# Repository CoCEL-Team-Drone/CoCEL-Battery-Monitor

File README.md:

# CoCEL LiPo Battery Monitor

**A high-current LiPo battery monitor with individual cell voltage sensing**

[!IMPORTANT] 
This project is currently under development! Especially cell voltage monitoring circuit. Please stay tuned for future updates.

The CoCEL LiPo Battery Monitor is a dedicated power management and monitoring solution for multicopters. It measures total pack voltage, discharge current, and individual cell voltages, interfacing with a FC via UART.

## 1. Core Specifications

### Power
- **Voltage:** 4s~6s LiPo (14.8 V ~ 25.2 V)
- **Current:** 200 A continuous
- **Output Cutoff:** Main power output can be cut off via a physical arming switch (shorting pins) or via UART commands
- **Aux Power Output:**
    - 3.3 V (3 A)
    - 5 V (3 A)
    - Input Bypass: Dedicated power rail for an SBC (remains active even when the main output is cut off)

### Connectivity
- **Interfaces:** 
    - **Communication:** 1x UART
    - **Visual Feedback:** 1x Diagnostic LED
    - **Firmware update:** Test points are used for firmware updates (SWDIO, SWCLK, NRST).

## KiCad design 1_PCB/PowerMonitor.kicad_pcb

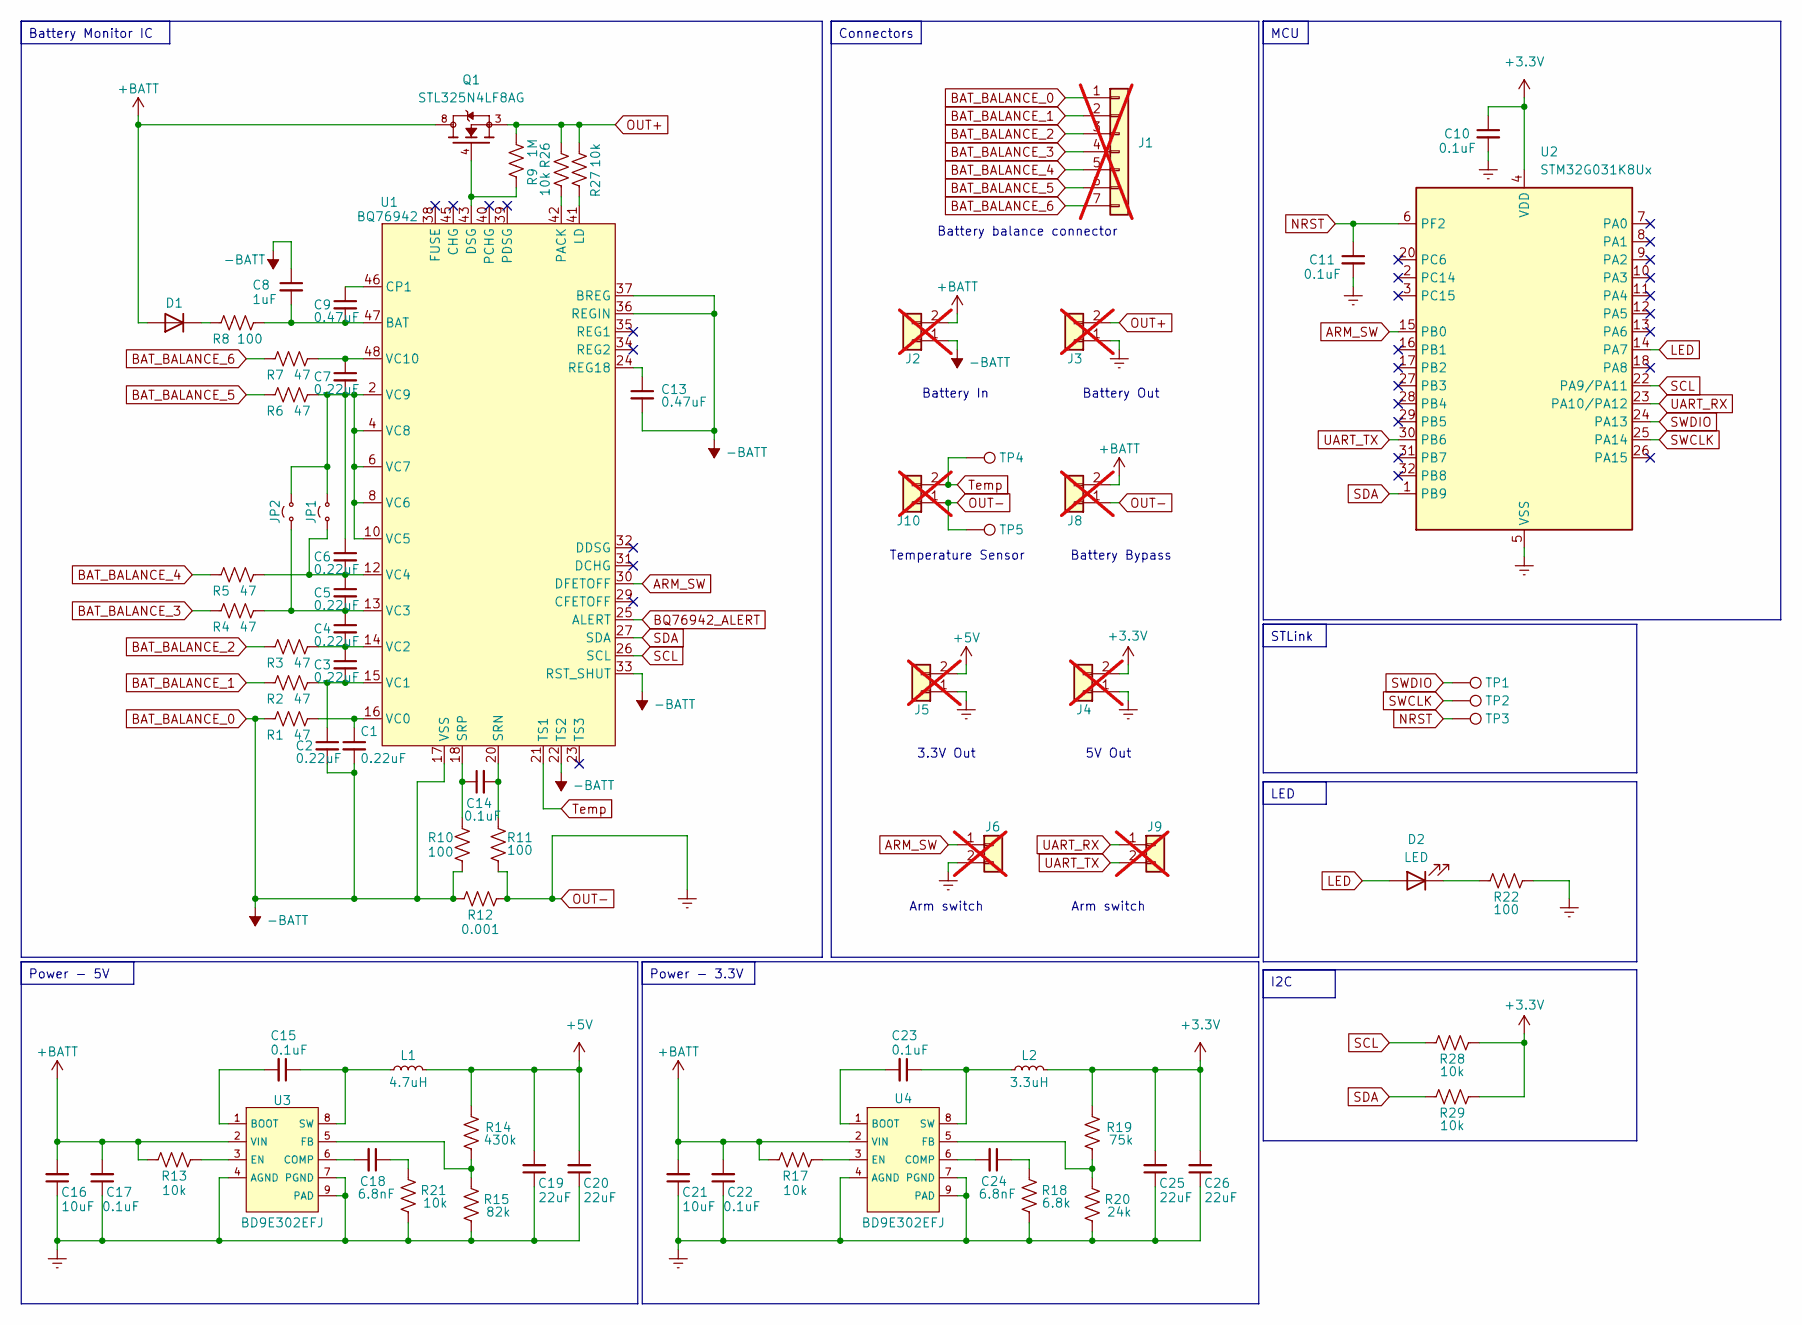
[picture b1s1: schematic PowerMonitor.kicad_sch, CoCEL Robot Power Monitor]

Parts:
C1, C2, C3, C4, C5, C6, C7: 0.22uF; C_0402_1005Metric
C8: 1uF; C_0402_1005Metric
C9, C13: 0.47uF; C_0402_1005Metric
C10, C11, C14: 0.1uF; C_0402_1005Metric
C15, C17, C22, C23: 0.1uF; C_0603_1608Metric
C16, C21: 10uF; C_1210_3225Metric
C18, C24: 6.8nF; C_0402_1005Metric_Pad0.74x0.62mm_HandSolder
C19, C20, C25, C26: 22uF; C_1210_3225Metric
D1: S1AFL; D_SOD-123
D2: LED; LED_0603_1608Metric
J1: Conn_01x07; Molex_KK-254_AE-6410-07A_1x07_P2.54mm_Vertical; not fitted
J2: Conn_01x02; AMASS_XT60-M_1x02_P7.20mm_Vertical; not fitted
J3: Conn_01x02; AMASS_XT60-F_1x02_P7.20mm_Vertical; not fitted
J4, J5, J6, J9, J10: Conn_01x02; PinHeader_1x02_P2.54mm_Vertical; not fitted
J8: Conn_01x02; AMASS_XT30U-F_1x02_P5.0mm_Vertical; not fitted
JP1, JP2: Jumper_2_Small_Open; SolderJumper-2_P1.3mm_Open_TrianglePad1.0x1.5mm
L1: 4.7uH; L_7.3x7.3_H4.5
L2: 3.3uH; L_7.3x7.3_H4.5
Q1: STL325N4LF8AG; ST_PowerFLAT-6L_5x6mm_P1.27mm
R1, R2, R3, R4, R5, R6, R7: 47; R_0402_1005Metric
R8, R10, R11, R22: 100; R_0402_1005Metric
R9: 1M; R_0402_1005Metric
R12: 0.001; R_3920_10052Metric
R13, R17, R21, R26, R27, R28, R29: 10k; R_0402_1005Metric
R14: 430k; R_0402_1005Metric
R15: 82k; R_0402_1005Metric
R18: 6.8k; R_0402_1005Metric
R19: 75k; R_0402_1005Metric
R20: 24k; R_0402_1005Metric
TP1, TP2, TP3, TP4, TP5: TestPoint; TestPoint_Pad_D1.0mm
U1: BQ76942; TQFP-48_7x7mm_P0.5mm
U2: STM32G031K8Ux; QFN-32-1EP_5x5mm_P0.5mm_EP3.45x3.45mm
U3, U4: BD9E302EFJ; HTSOP-8-1EP_3.9x4.9mm_P1.27mm_EP2.4x3.2mm

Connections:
+3.3V: C10.1, C25.2, C26.2, J4.2, L2.2, R19.2, R28.2, R29.2, U2.4 (VDD)
+5V: C19.2, C20.2, J5.2, L1.2, R14.2
+BATT: C16.2, C17.2, C21.2, C22.2, D1.2 (A), J2.2, J8.2, Q1.5, Q1.6, Q1.7, Q1.8, R13.1, R17.1, U3.2 (VIN), U4.2 (VIN)
ARM_SW: J6.1, U1.30 (DFETOFF), U2.15 (PB0)
BAT_BALANCE_0: C1.2, C2.2, C8.1, C13.2, J1.1, J2.1, R1.1, R10.2, R12.2, U1.17 (VSS), U1.22 (TS2), U1.33 (RST_SHUT), U1.36 (REGIN), U1.37 (BREG)
BAT_BALANCE_1: J1.2, R2.1
BAT_BALANCE_2: J1.3, R3.1
BAT_BALANCE_3: J1.4, R4.1
BAT_BALANCE_4: J1.5, R5.1
BAT_BALANCE_5: J1.6, R6.1
BAT_BALANCE_6: J1.7, R7.1
BQ76942_ALERT: U1.25 (ALERT)
LED: D2.2 (A), U2.14 (PA7)
NRST: C11.1, TP3.1 (1_1), U2.6 (PF2)
unnamed: C18.1, R21.2
unnamed: C24.1, R18.2
unnamed: D1.1 (K), R8.1
unnamed: D2.1 (K), R22.1
unnamed: C5.1, C6.2, JP1.1 (A), R5.2, U1.12 (VC4)
unnamed: C6.1, C7.2, JP1.2 (B), JP2.2 (B), R6.2, U1.2 (VC9), U1.4 (VC8), U1.6 (VC7), U1.8 (VC6), U1.10 (VC5)
unnamed: C4.1, C5.2, JP2.1 (A), R4.2, U1.13 (VC3)
unnamed: C8.2, C9.2, R8.2, U1.47 (BAT)
unnamed: C9.1, U1.46 (CP1)
unnamed: Q1.4, R9.1, U1.43 (DSG)
unnamed: R27.1, U1.41 (LD)
unnamed: R26.2, U1.42 (PACK)
unnamed: C13.1, U1.24 (REG18)
unnamed: C14.2, R11.2, U1.20 (SRN)
unnamed: C14.1, R10.1, U1.18 (SRP)
unnamed: C1.1, R1.2, U1.16 (VC0)
unnamed: C2.1, C3.2, R2.2, U1.15 (VC1)
unnamed: C3.1, C4.2, R3.2, U1.14 (VC2)
unnamed: C7.1, R7.2, U1.48 (VC10)
unnamed: C15.2, U3.1 (BOOT)
unnamed: C18.2, U3.6 (COMP)
unnamed: R13.2, U3.3 (EN)
unnamed: R14.1, R15.2, U3.5 (FB)
unnamed: C15.1, L1.1, U3.8 (SW)
unnamed: C23.2, U4.1 (BOOT)
unnamed: C24.2, U4.6 (COMP)
unnamed: R17.2, U4.3 (EN)
unnamed: R19.1, R20.2, U4.5 (FB)
unnamed: C23.1, L2.1, U4.8 (SW)
OUT+: J3.2, Q1.1, Q1.2, Q1.3, R9.2, R26.1, R27.2
OUT-: C10.2, C11.2, C16.1, C17.1, C19.1, C20.1, C21.1, C22.1, C25.1, C26.1, J3.1, J4.1, J5.1, J6.2, J8.1, J10.1, R11.1, R12.1, R15.1, R18.1, R20.1, R21.1, R22.2, TP5.1 (1_1), U2.5 (VSS), U2.33 (VSS), U3.4 (AGND), U3.7 (PGND), U3.9 (PAD), U4.4 (AGND), U4.7 (PGND), U4.9 (PAD)
SCL: R28.1, U1.26 (SCL), U2.22 (PA9/PA11)
SDA: R29.1, U1.27 (SDA), U2.1 (PB9)
SWCLK: TP2.1 (1_1), U2.25 (PA14)
SWDIO: TP1.1 (1_1), U2.24 (PA13)
Temp: J10.2, TP4.1 (1_1), U1.21 (TS1)
UART_RX: J9.1, U2.23 (PA10/PA12)
UART_TX: J9.2, U2.30 (PB6)

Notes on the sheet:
Battery balance connector
Temperature Sensor
Arm switch
Battery Bypass
Battery Out
Battery In
5V Out
3.3V Out
Battery Monitor IC
STLink
LED
Power - 5V
Connectors
I2C
Power - 3.3V
MCU

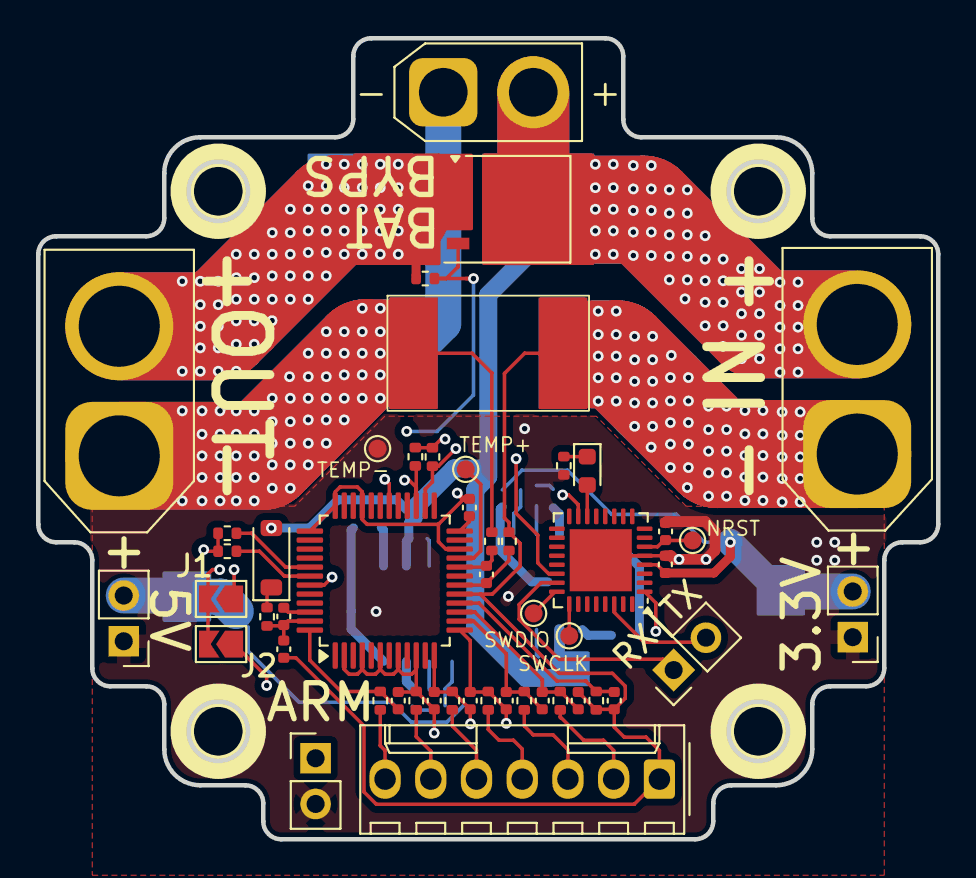
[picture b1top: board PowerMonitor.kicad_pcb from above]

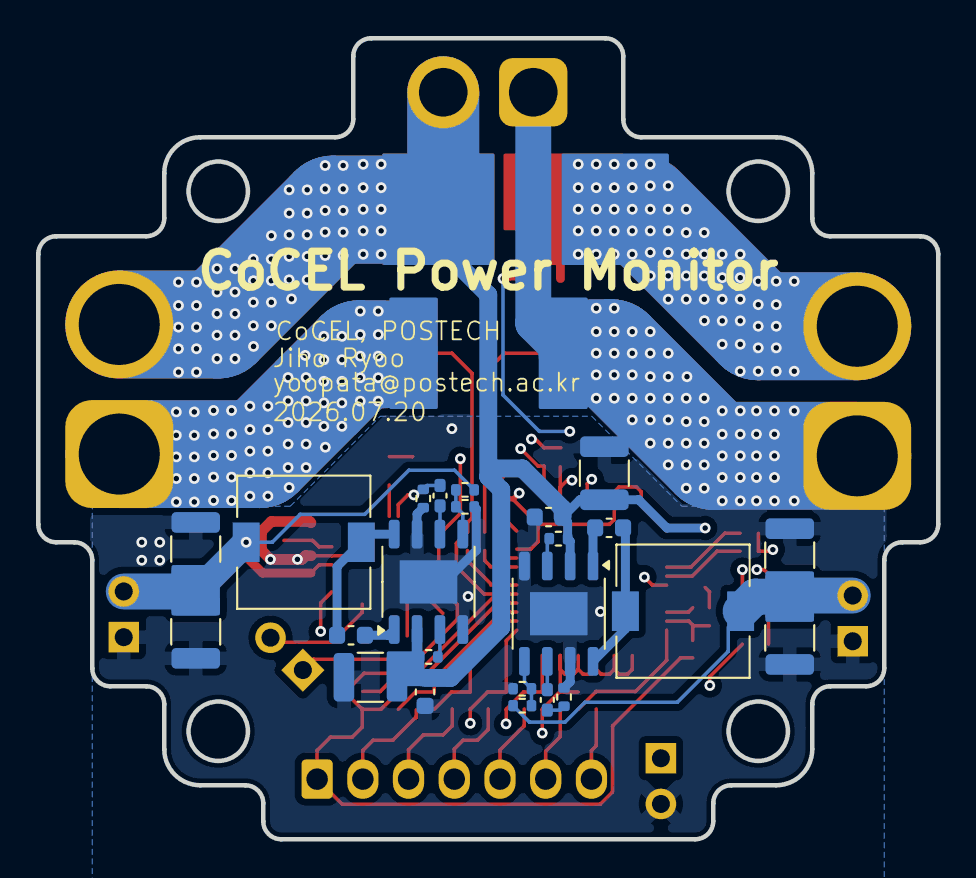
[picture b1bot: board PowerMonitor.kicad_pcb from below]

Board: 4 copper layers, 50.0 x 44.5 mm, 74 parts (24 on the bottom side), 51 nets.

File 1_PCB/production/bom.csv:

Designator,Footprint,Quantity,Value,LCSC Part #
"C1, C2, C3, C4, C5, C6, C7",0402,7,0.22uF,
"C10, C14",0402,2,0.1uF,
"C15, C17, C22, C23",0603,4,0.1uF,
"C16, C21",1210,2,10uF,
"C18, C24",0402,2,6.8nF,
"C19, C20, C25, C26",1210,4,22uF,
C8,0402,1,1uF,
C9,0402,1,0.47uF,
D1,D_SOD-123,1,S1AFL,
D2,0603,1,LED,
"JP1, JP2",SolderJumper-2_P1.3mm_Open_TrianglePad1.0x1.5mm,2,Jumper_2_Small_Open,
L1,L_7.3x7.3_H4.5,1,4.7uH,
L2,L_7.3x7.3_H4.5,1,3.3uH,
Q1,ST_PowerFLAT-6L_5x6mm_P1.27mm,1,STL325N4LF8AG,
"R1, R2, R3, R4, R5, R6, R7",0402,7,47,
"R10, R11, R22, R8",0402,4,100,
R12,3920,1,0.001,
"R13, R17, R21, R26, R27",0402,5,10k,
R14,0402,1,430k,
R15,0402,1,82k,
R18,0402,1,6.8k,
R19,0402,1,75k,
R20,0402,1,24k,
R9,0402,1,1M,
U1,TQFP-48_7x7mm_P0.5mm,1,BQ76942,
U2,QFN-32-1EP_5x5mm_P0.5mm_EP3.45x3.45mm,1,STM32G031K8Ux,
"U3, U4",HTSOP-8-1EP_3.9x4.9mm_P1.27mm_EP2.4x3.2mm,2,BD9E302EFJ,

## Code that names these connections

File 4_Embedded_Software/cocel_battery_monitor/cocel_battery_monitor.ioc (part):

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Mcu.Name=STM32G031K(4-6-8)Ux
Mcu.Package=UFQFPN32
Mcu.UserName=STM32G031K8Ux
PA10\ [PA12].Mode=Asynchronous
PA10\ [PA12].Signal=USART1_RX
PA13.Mode=Serial_Wire
PA13.Signal=SYS_SWDIO
PA14-BOOT0.Mode=Serial_Wire
PA14-BOOT0.Signal=SYS_SWCLK
PA7.GPIOParameters=GPIO_Label
PA7.GPIO_Label=LED
PA7.Signal=GPIO_Output
PA9\ [PA11].Mode=I2C
PA9\ [PA11].Signal=I2C1_SCL
PB0.GPIOParameters=GPIO_Label
PB0.GPIO_Label=ARM_SW
PB0.Signal=GPIO_Output
PB6.Mode=Asynchronous
PB6.Signal=USART1_TX
PB9.Mode=I2C
PB9.Signal=I2C1_SDA
RCC.HSE_VALUE=8000000
RCC.SYSCLKFreq_VALUE=64000000
RCC.SYSCLKSource=RCC_SYSCLKSOURCE_PLLCLK
board=custom

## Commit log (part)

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2026-04-14 add README
2026-05-29 added schematic pdf
